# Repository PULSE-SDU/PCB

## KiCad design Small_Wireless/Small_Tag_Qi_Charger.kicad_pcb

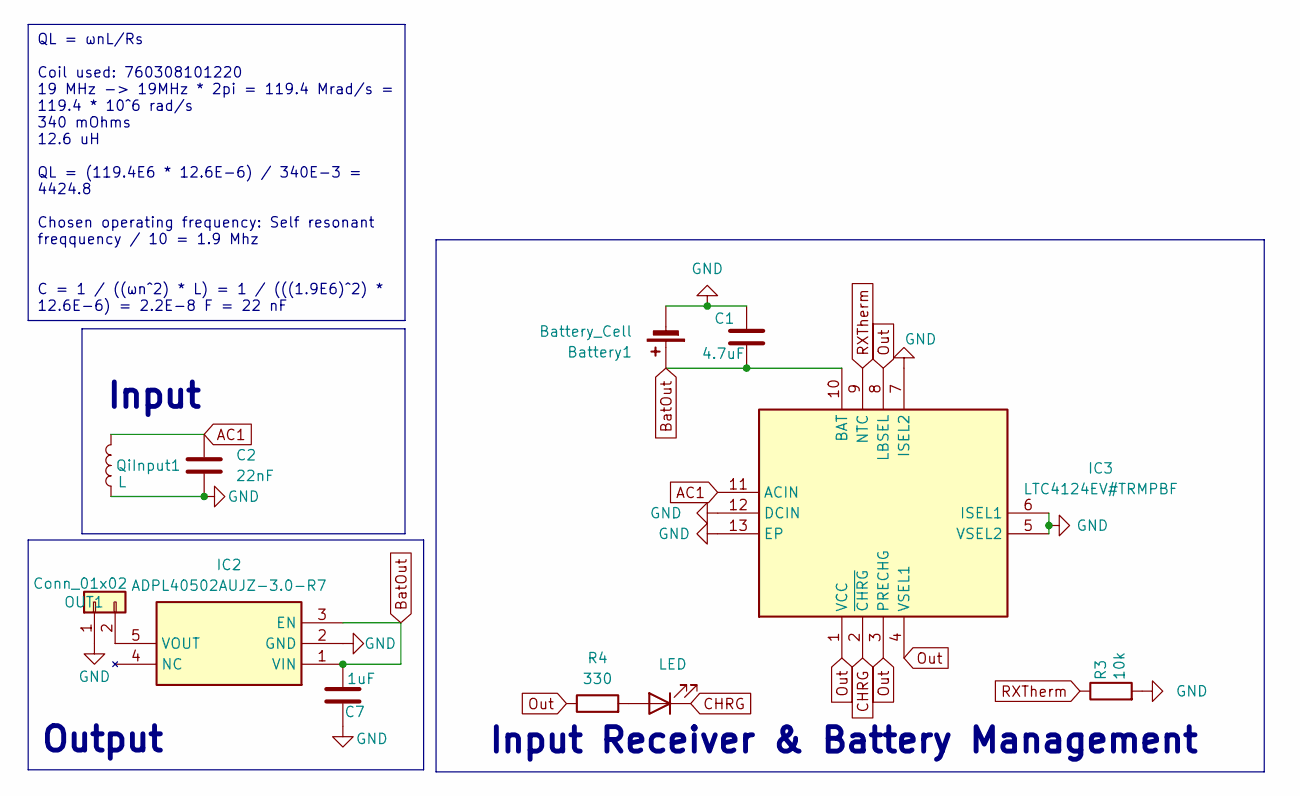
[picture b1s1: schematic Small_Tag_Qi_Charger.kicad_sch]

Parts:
Battery1: Battery_Cell; PinHeader_1x02_P2.54mm_Vertical
C1: 4.7uF; C_0402_1005Metric_Pad0.74x0.62mm_HandSolder
C2: 22nF; C_0402_1005Metric_Pad0.74x0.62mm_HandSolder
C7: 1uF; C_0402_1005Metric_Pad0.74x0.62mm_HandSolder
D2: LED; LED_0402_1005Metric_Pad0.77x0.64mm_HandSolder
IC2: ADPL40502AUJZ-3.0-R7; SOT95P280X100-5N; Mouser Part Number 584-ADPL40502AUJZ30R
IC3: LTC4124EV#TRMPBF; QFN50P200X200X83-13N-D; Mouser Part Number 584-LTC4124EV#TRMPBF
OUT1: Conn_01x02; PinHeader_1x02_P2.54mm_Vertical
QiInput1: L; PinHeader_1x02_P2.54mm_Vertical
R3: 10k; R_0402_1005Metric_Pad0.72x0.64mm_HandSolder
R4: 330; R_0402_1005Metric_Pad0.72x0.64mm_HandSolder

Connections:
AC1: C2.1, IC3.11 (ACIN), QiInput1.2
BatOut: Battery1.1 (+), C1.2, C7.2, IC2.1 (VIN), IC2.3 (EN), IC3.10 (BAT)
CHRG: D2.1 (K), IC3.2 (~CHRG)
GND: Battery1.2 (-), C1.1, C2.2, C7.1, IC2.2 (GND), IC3.5 (VSEL2), IC3.6 (ISEL1), IC3.7 (ISEL2), IC3.12 (DCIN), IC3.13 (EP), OUT1.1, QiInput1.1, R3.2
unnamed: D2.2 (A), R4.2
unnamed: IC2.5 (VOUT), OUT1.2
Out: IC3.1 (VCC), IC3.3 (PRECHG), IC3.4 (VSEL1), IC3.8 (LBSEL), R4.1
RXTherm: IC3.9 (NTC), R3.1

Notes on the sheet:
QL = ωnL/Rs Coil used: 760308101220 19 MHz -> 19MHz * 2pi = 119.4 Mrad/s = 119.4 * 10^6 rad/s 340 mOhms 12.6 uH QL = (119.4E6 * 12.6E-6) / 340E-3 = 4424.8 Chosen operating frequency: Self resonant freqquency / 10 = 1.9 Mhz C = 1 / ((ωn^2) * L) = 1 / (((1.9E6)^2) * 12.6E-6) = 2.2E-8 F = 22 nF
Input Receiver & Battery Management
Input
Output

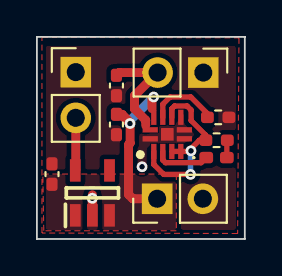
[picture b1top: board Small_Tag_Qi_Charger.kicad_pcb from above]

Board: 2 copper layers, 11.6 x 11.2 mm, 11 parts (0 on the bottom side), 8 nets.

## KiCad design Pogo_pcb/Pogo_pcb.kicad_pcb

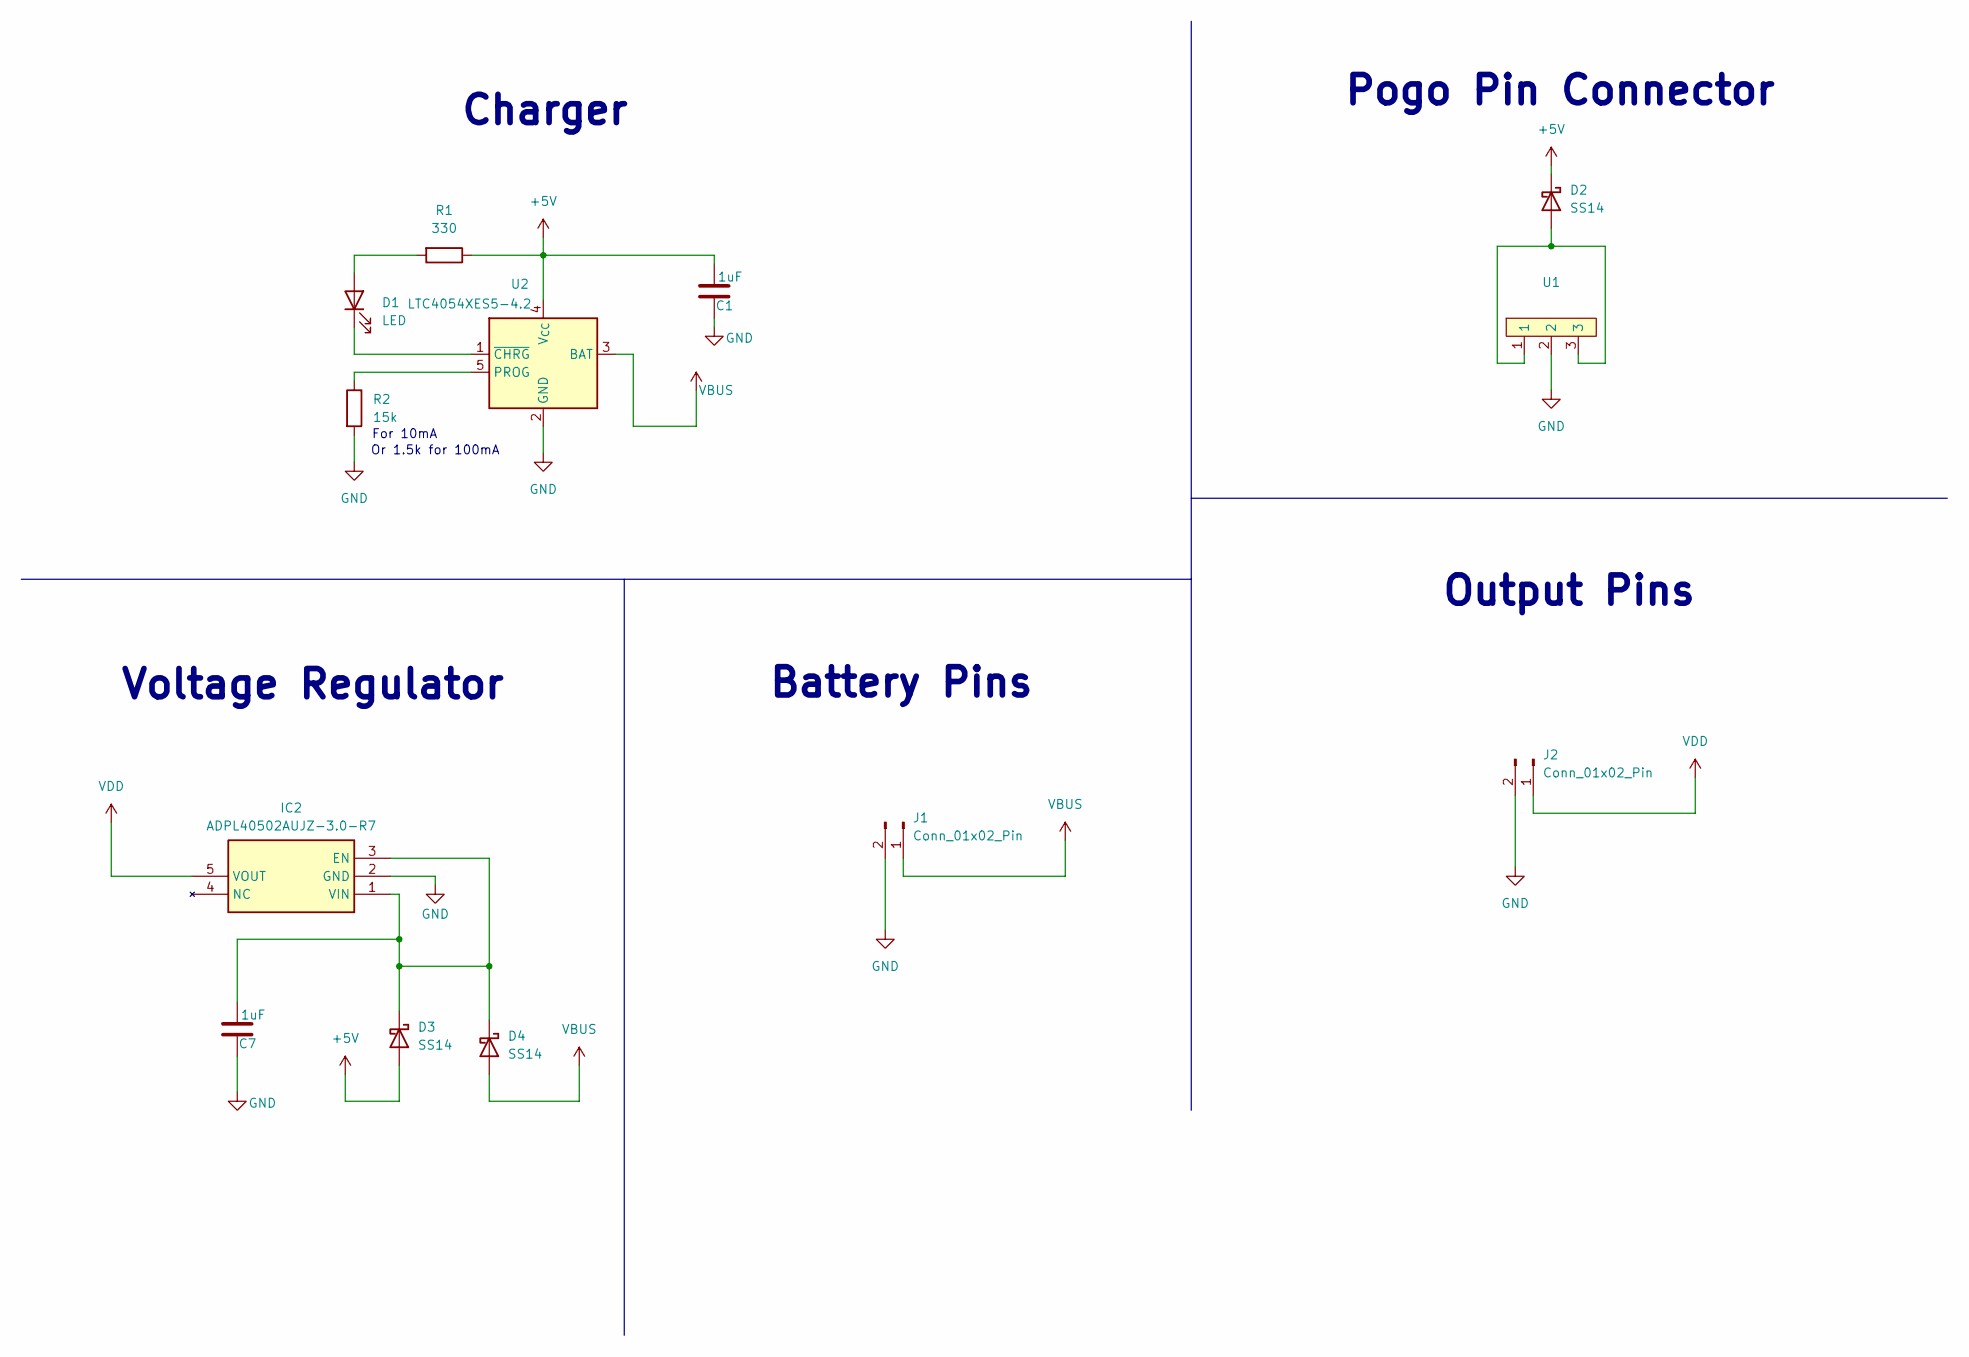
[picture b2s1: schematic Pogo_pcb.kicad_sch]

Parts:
C1, C7: 1uF; C_0805_2012Metric_Pad1.18x1.45mm_HandSolder
D1: LED; LED_0402_1005Metric_Pad0.77x0.64mm_HandSolder
D2, D3, D4: SS14; D_SMA
IC2: ADPL40502AUJZ-3.0-R7; SOT-23-5_HandSoldering; Mouser Part Number 584-ADPL40502AUJZ30R
J1, J2: Conn_01x02_Pin; PinSocket_1x02_P2.54mm_Vertical
R1: 330; R_0402_1005Metric_Pad0.72x0.64mm_HandSolder
R2: 15k; R_0402_1005Metric_Pad0.72x0.64mm_HandSolder
U1: Pogo_pin
U2: LTC4054XES5-4.2; TSOT-23-5_HandSoldering

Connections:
+5V: C1.2, D2.1 (K), D3.2 (A), R1.1, U2.4 (V_{CC})
GND: C1.1, C7.1, IC2.2 (GND), J1.2, J2.2, R2.2, U1.2, U2.2 (GND)
unnamed: D1.2 (A), R1.2
unnamed: D1.1 (K), U2.1 (~CHRG)
unnamed: D2.2 (A), U1.1, U1.3
unnamed: C7.2, D3.1 (K), D4.1 (K), IC2.1 (VIN), IC2.3 (EN)
unnamed: R2.1, U2.5 (PROG)
VBUS: D4.2 (A), J1.1, U2.3 (BAT)
VDD: IC2.5 (VOUT), J2.1

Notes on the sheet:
Voltage Regulator
Charger
For 10mA
Output Pins
Pogo Pin Connector
Battery Pins
Or 1.5k for 100mA

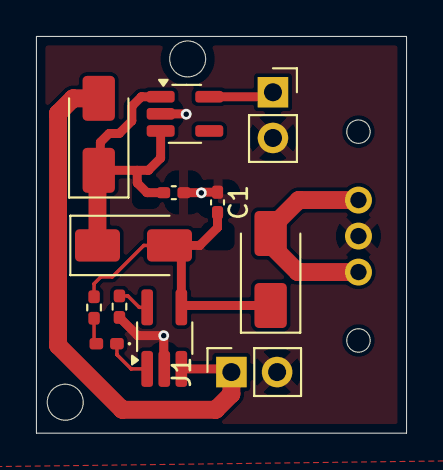
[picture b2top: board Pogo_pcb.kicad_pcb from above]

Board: 2 copper layers, 20.6 x 22.0 mm, 13 parts (0 on the bottom side), 9 nets.

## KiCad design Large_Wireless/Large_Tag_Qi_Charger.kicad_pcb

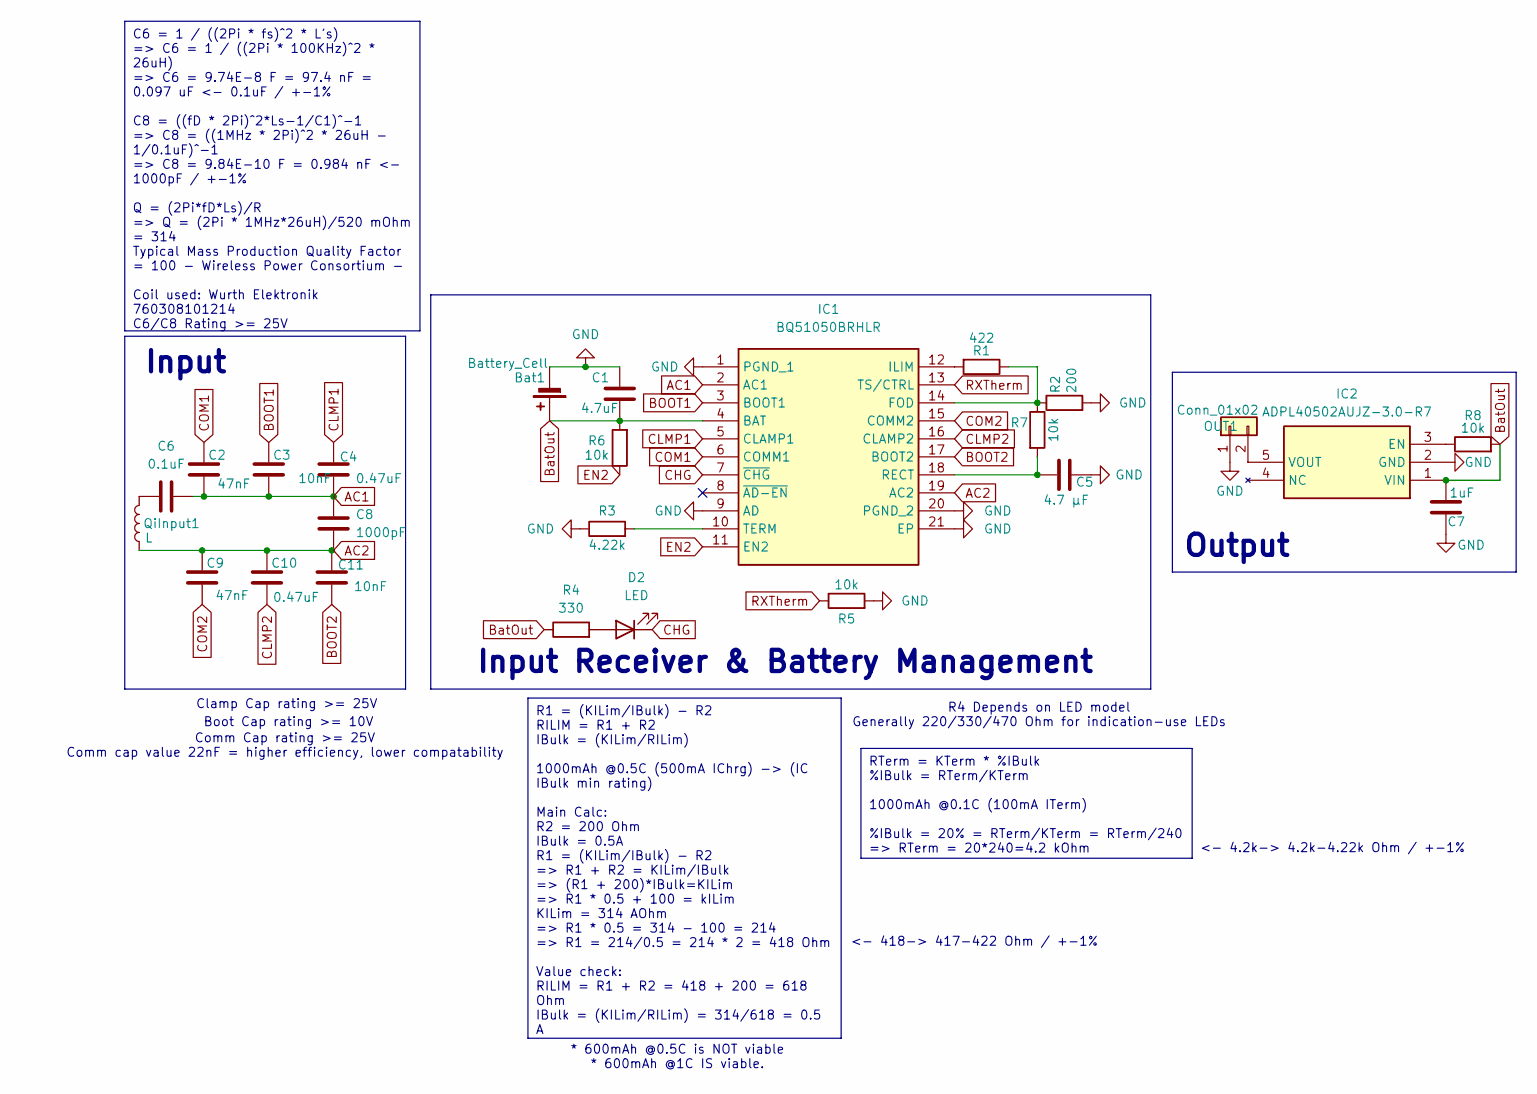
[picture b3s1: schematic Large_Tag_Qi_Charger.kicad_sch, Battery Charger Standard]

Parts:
Bat1: Battery_Cell; PinHeader_1x02_P2.54mm_Vertical
C1: 4.7uF; C_0805_2012Metric_Pad1.18x1.45mm_HandSolder
C2, C9: 47nF; C_0805_2012Metric_Pad1.18x1.45mm_HandSolder
C3, C11: 10nF; C_0805_2012Metric_Pad1.18x1.45mm_HandSolder
C4, C10: 0.47uF; C_0805_2012Metric_Pad1.18x1.45mm_HandSolder
C5: 4.7 μF; C_0805_2012Metric_Pad1.18x1.45mm_HandSolder
C6: 0.1uF; C_0805_2012Metric_Pad1.18x1.45mm_HandSolder
C7: 1uF; C_0805_2012Metric_Pad1.18x1.45mm_HandSolder
C8: 1000pF; C_0805_2012Metric_Pad1.18x1.45mm_HandSolder
D2: LED; D_0805_2012Metric_Pad1.15x1.40mm_HandSolder
IC1: BQ51050BRHLR; Mouser Part Number 595-BQ51050BRHLR
IC2: ADPL40502AUJZ-3.0-R7; SOT95P280X100-5N; Mouser Part Number 584-ADPL40502AUJZ30R
OUT1: Conn_01x02; PinHeader_1x02_P2.54mm_Vertical
QiInput1: L; PinHeader_1x02_P2.54mm_Vertical
R1: 422; R_0805_2012Metric_Pad1.20x1.40mm_HandSolder
R2: 200; R_0805_2012Metric_Pad1.20x1.40mm_HandSolder
R3: 4.22k; R_0805_2012Metric_Pad1.20x1.40mm_HandSolder
R4: 330; R_0805_2012Metric_Pad1.20x1.40mm_HandSolder
R5, R6, R7, R8: 10k; R_0805_2012Metric_Pad1.20x1.40mm_HandSolder

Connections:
AC1: C2.2, C3.2, C4.2, C6.1, C8.1, IC1.2 (AC1)
AC2: C8.2, C9.1, C10.1, C11.1, IC1.19 (AC2), QiInput1.1
BOOT1: C3.1, IC1.3 (BOOT1)
BOOT2: C11.2, IC1.17 (BOOT2)
BatOut: Bat1.1 (+), C1.2, C7.2, IC1.4 (BAT), IC2.1 (VIN), R4.1, R6.2, R8.2
CHG: D2.1 (K), IC1.7 (~CHG)
CLMP1: C4.1, IC1.5 (CLAMP1)
CLMP2: C10.2, IC1.16 (CLAMP2)
COM1: C2.1, IC1.6 (COMM1)
COM2: C9.2, IC1.15 (COMM2)
EN2: IC1.11 (EN2), R6.1
GND: Bat1.2 (-), C1.1, C5.1, C7.1, IC1.1 (PGND_1), IC1.9 (AD), IC1.20 (PGND_2), IC1.21 (EP), IC2.2 (GND), OUT1.1, R2.2, R3.1, R5.2
unnamed: C6.2, QiInput1.2
unnamed: D2.2 (A), R4.2
unnamed: IC1.14 (FOD), R1.1, R2.1, R7.1
unnamed: IC1.12 (ILIM), R1.2
unnamed: C5.2, IC1.18 (RECT), R7.2
unnamed: IC1.10 (TERM), R3.2
unnamed: IC2.3 (EN), R8.1
unnamed: IC2.5 (VOUT), OUT1.2
RXTherm: IC1.13 (TS/CTRL), R5.1

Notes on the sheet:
R1 = (KILim/IBulk) - R2 RILIM = R1 + R2 IBulk = (KILim/RILim) 1000mAh @0.5C (500mA IChrg) -> (IC IBulk min rating) Main Calc: R2 = 200 Ohm IBulk = 0.5A R1 = (KILim/IBulk) - R2 => R1 + R2 = KILim/IBulk => (R1 + 200)*IBulk=KILim => R1 * 0.5 + 100 = kILim KILim = 314 AOhm => R1 * 0.5 = 314 - 100 = 214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
C6 = 1 / ((2Pi * fs)^2 * L's) => C6 = 1 / ((2Pi * 100KHz)^2 * 26uH) => C6 = 9.74E-8 F = 97.4 nF = 0.097 uF <- 0.1uF / +-1% C8 = ((fD * 2Pi)^2*Ls-1/C1)^-1 => C8 = ((1MHz * 2Pi)^2 * 26uH - 1/0.1uF)^-1 => C8 = 9.84E-10 F = 0.984 nF <- 1000pF / +-1% Q = (2Pi*fD*Ls)/R => Q = (2Pi * 1MHz*26uH)/520 mOhm =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
RTerm = KTerm * %IBulk %IBulk = RTerm/KTerm 1000mAh @0.1C (100mA ITerm) %IBulk = 20% = RTerm/KTerm = RTerm/240 => RTerm = 20*240=4.2 kOhm
Input Receiver & Battery Management
* 600mAh @0.5C is NOT viable * 600mAh @1C IS viable.
R4 Depends on LED model Generally 220/330/470 Ohm for indication-use LEDs
Input
<- 4.2k-> 4.2k-4.22k Ohm / +-1%
Comm Cap rating >= 25V Comm cap value 22nF = higher efficiency, lower compatability
Boot Cap rating >= 10V
Output
Clamp Cap rating >= 25V
<- 418-> 417-422 Ohm / +-1%

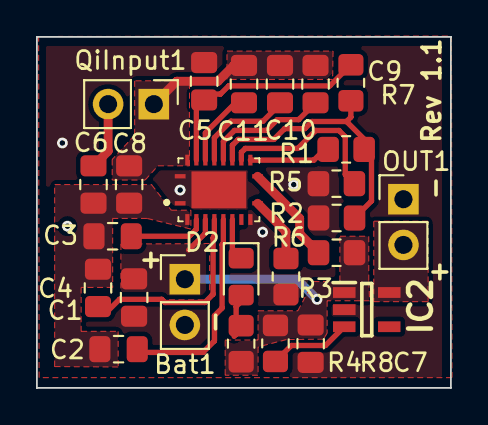
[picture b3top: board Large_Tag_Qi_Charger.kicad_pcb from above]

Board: 2 copper layers, 23.0 x 19.5 mm, 25 parts (0 on the bottom side), 21 nets.

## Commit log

2025-11-20 Large Tag PCB
2025-11-23 Pogo PCB
2025-11-23 Small Wireless
